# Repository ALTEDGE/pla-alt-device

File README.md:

# pla-alt-device

This repository contains the source code and hardware design files for the PLA ALT Avatar Motion Controller.

To compile the source code, use the [Arduino IDE](https://www.arduino.cc/en/software). After running the Arduino IDE, an `Arduino` folder is created in your Documents folder. Copy the `hardware` folder in this repo into that `Arudino` folder; then, the Arduino IDE should show "PLA ALT" as a board option.

The controller's hardware was designed using [EAGLE](https://www.autodesk.com/products/eagle/overview). Schematic and board files are located in the `eagle` folder.

## Brief user guide

The controller appears to the computer as a regular gaming joystick/controller. The [PLA ALT GUI](https://github.com/ALTEDGE/pla-alt-gui) must be running in order to use the controller to its full potential.

To reprogram the ALT controller, put it into programming mode by holding down the right joystick button while plugging into the computer; the LEDs should not turn on. After uploading new code through the IDE, reconnect the controller.

The ALT controller self-calibrates when it is first powered on. If recalibration is ever necessary, hold down the left joystick button while plugging into the computer. Release the button once the LEDs light up white. Calibration is finished once the LEDs return to blue.

### Licensing

The ALT controller's source code is licensed under the GNU GPLv3; see the LICENSE file in the top directory. The controller's hardware files (EAGLE schematic and board files) are licensed under the TAPR Open Hardware License; see the LICENSE file in the `eagle` folder.

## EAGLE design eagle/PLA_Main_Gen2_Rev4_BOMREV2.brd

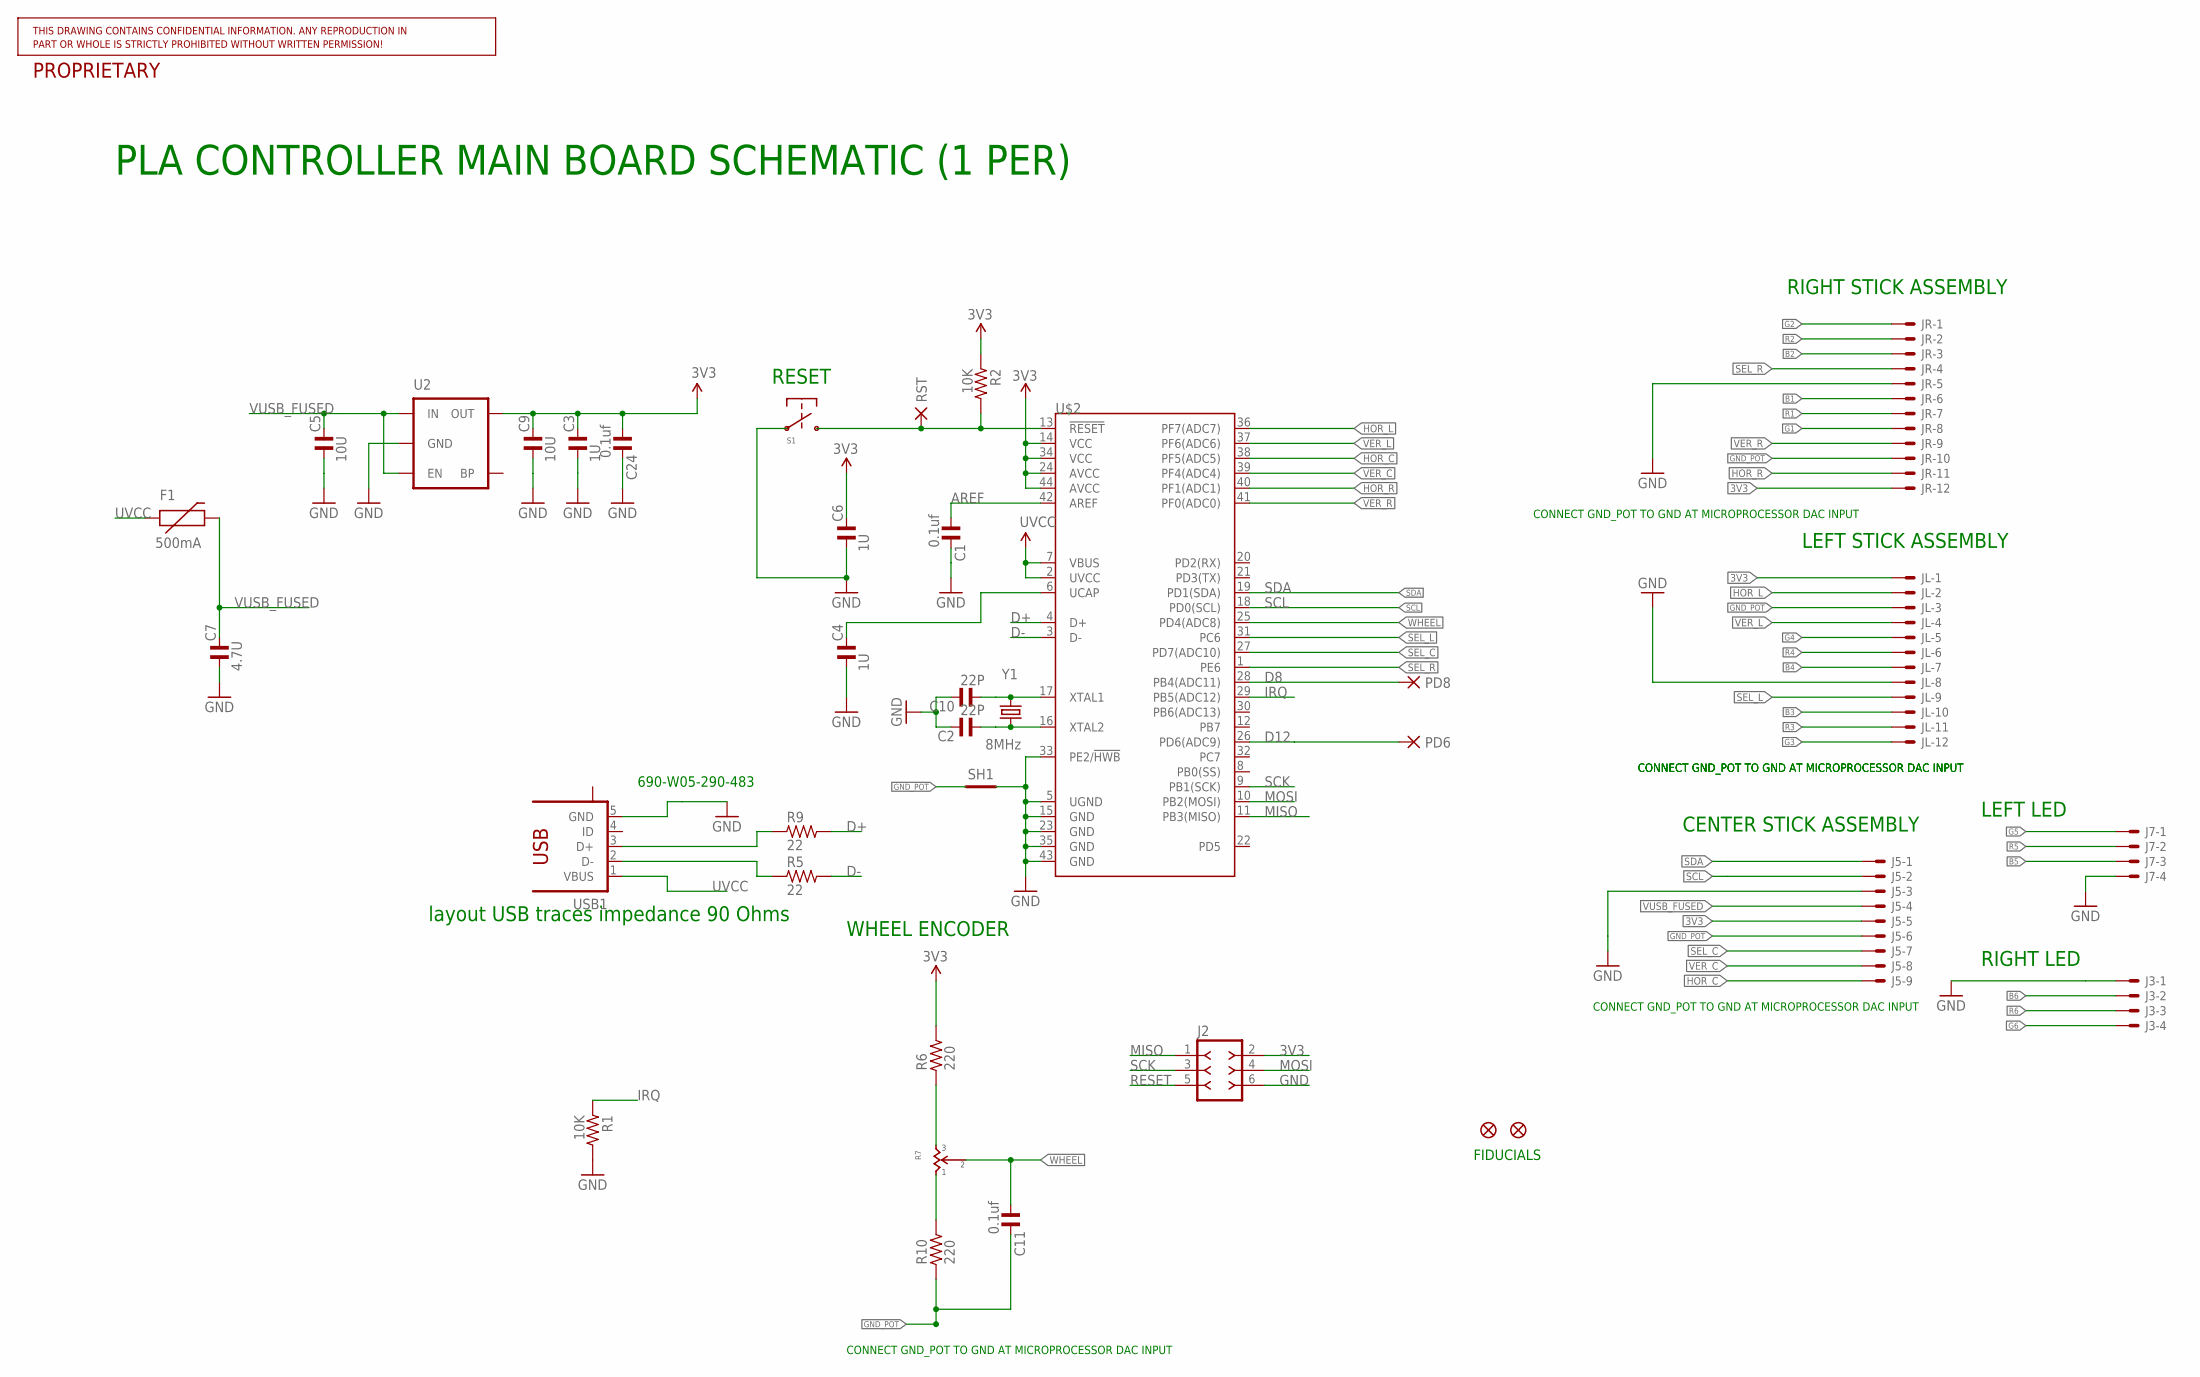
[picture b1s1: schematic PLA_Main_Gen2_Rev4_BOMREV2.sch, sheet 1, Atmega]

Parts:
C1, C11, C24: 0.1uf; C0603; PARTNO 64K2839
C2, C10: 22P; C0603; PARTNO 06035C220JAT2A
C3, C4, C6: 1U; C0603; PARTNO CL10B105KP8NNNC
C5, C9: 10U; C1206; PARTNO C3216X5R1H106K160AB
C7: 4.7U; C0603; PARTNO GRM188R61A475KE15D
F1: 500mA; PTC-1206; PARTNO NANOSMDH075F-02
J2: F-2X03-DIL-100; DIL-100-2X03; PARTNO *
J3, J7: SM04B-SRSS-TB; PARTNO SM04B-SRSS-TB(LF)(SN)
J5: SM09B-SRSS-TB; PARTNO SM09B-SRSS-TB
JL: SM12B-SRSS-TB; PARTNO SM12B-SRSS-TB(LF)(SN)
JP1, JP2: FIDUCIALUFIDUCIAL; MICRO-FIDUCIAL; PARTNO *
JR: SM12B-SRSS-TB; PARTNO SM12B-SRSS-TB(LF)(SN)
PD6, PD8: PAD-SMD12R; SMD12R
R1, R2: 10K; R0603; PARTNO ERJ-PA3J103V
R5, R9: 22; R0603; PARTNO ERJ-PA3J220V
R6, R10: 220; R0603; PARTNO ERJ-PA3J221V
R7: SV01A103AEA01R00; PARTNO SV01A103AEA01R00
RST: PAD-SMD10R; SMD10R
S1: KMR211GLFS; PARTNO KMR211GLFS
SH1: SHORTT5; SHORT_TOP-50; PARTNO *
U2: V_REG_LDOSMD; SOT23-5; PARTNO MIC5219-3.3YM5-TR
U$2: ATMEGA32U4QFN; QFN-44; PARTNO ATMEGA32U4-MU
USB1: 10118192-0001LF; PARTNO 10118192-0001LF
Y1: 8MHz; CRYSTAL-SMD-5X3; PARTNO ABM3B-8.000MHZ-B2-T

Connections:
3V3: C3.2, C6.2, C9.2, C24.1, J2.2, J5.5, JL.1, JR.12, R2.1, R6.2, U2.5 (OUT), U$2.14 (VCC), U$2.24 (AVCC), U$2.34 (VCC), U$2.44 (AVCC); also elsewhere on the board
AREF: C1.1, U$2.42 (AREF)
B1: JR.6; also elsewhere on the board
B2: JR.3; also elsewhere on the board
B3: JL.10; also elsewhere on the board
B4: JL.7; also elsewhere on the board
B5: J7.3; also elsewhere on the board
B6: J3.2; also elsewhere on the board
D8: PD8.PAD, U$2.28 (PB4(ADC11))
D12: PD6.PAD, U$2.26 (PD6(ADC9))
D+: R9.2, U$2.4 (D+)
D-: R5.2, U$2.3 (D-)
G1: JR.8; also elsewhere on the board
G2: JR.1; also elsewhere on the board
G3: JL.12; also elsewhere on the board
G4: JL.5; also elsewhere on the board
G5: J7.1; also elsewhere on the board
G6: J3.4; also elsewhere on the board
GND: C1.2, C2.2, C3.1, C4.1, C5.1, C6.1, C7.1, C9.1, C10.2, C24.2, J2.6, J3.1, J5.3, J7.4, JL.8, JR.5, R1.2, S1.1A (1), S1.1B (1), SH1.2, U2.2 (GND), U$2.5 (UGND), U$2.15 (GND), U$2.23 (GND), U$2.33 (PE2/!HWB), U$2.35 (GND), U$2.43 (GND), USB1.5 (GND); also elsewhere on the board
GND_POT: C11.2, J5.6, JL.3, JR.10, R10.1, SH1.1
HOR_C: J5.9, U$2.38 (PF5(ADC5))
HOR_L: JL.2, U$2.36 (PF7(ADC7))
HOR_R: JR.11, U$2.40 (PF1(ADC1))
IRQ: R1.1, U$2.29 (PB5(ADC12))
MISO: J2.1, U$2.11 (PB3(MISO))
MOSI: J2.4, U$2.10 (PB2(MOSI))
unnamed: C2.1, U$2.16 (XTAL2), Y1.1
unnamed: C10.1, U$2.17 (XTAL1), Y1.3 (2)
unnamed: C4.2, U$2.6 (UCAP)
unnamed: R6.1, R7.3
unnamed: R7.1, R10.2
R1: JR.7; also elsewhere on the board
R2: JR.2; also elsewhere on the board
R3: JL.11; also elsewhere on the board
R4: JL.6; also elsewhere on the board
R5: J7.2; also elsewhere on the board
R6: J3.3; also elsewhere on the board
RESET: J2.5, R2.2, RST.PAD, S1.2A (2), S1.2B (2), U$2.13 (!RESET)
SCK: J2.3, U$2.9 (PB1(SCK))
SCL: J5.2, U$2.18 (PD0(SCL)); also elsewhere on the board
SDA: J5.1, U$2.19 (PD1(SDA)); also elsewhere on the board
SEL_C: J5.7, U$2.27 (PD7(ADC10))
SEL_L: JL.9, U$2.31 (PC6)
SEL_R: JR.4, U$2.1 (PE6)
USB_N: R5.1, USB1.2 (D-)
USB_P: R9.1, USB1.3 (D+)
UVCC: F1.1, U$2.2 (UVCC), U$2.7 (VBUS), USB1.1 (VBUS)
VER_C: J5.8, U$2.39 (PF4(ADC4))
VER_L: JL.4, U$2.37 (PF6(ADC6))
VER_R: JR.9, U$2.41 (PF0(ADC0))
VUSB_FUSED: C5.2, C7.2, F1.2, J5.4, U2.1 (IN), U2.3 (EN); also elsewhere on the board
WHEEL: C11.1, R7.2, R7.2A (2), U$2.25 (PD4(ADC8))

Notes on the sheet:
690-W05-290-483
layout USB traces impedance 90 Ohms
LEFT STICK ASSEMBLY
CONNECT GND_POT TO GND AT MICROPROCESSOR DAC INPUT
RIGHT STICK ASSEMBLY
CENTER STICK ASSEMBLY
WHEEL ENCODER
RESET
LEFT LED
RIGHT LED
FIDUCIALS
PLA CONTROLLER MAIN BOARD SCHEMATIC (1 PER)

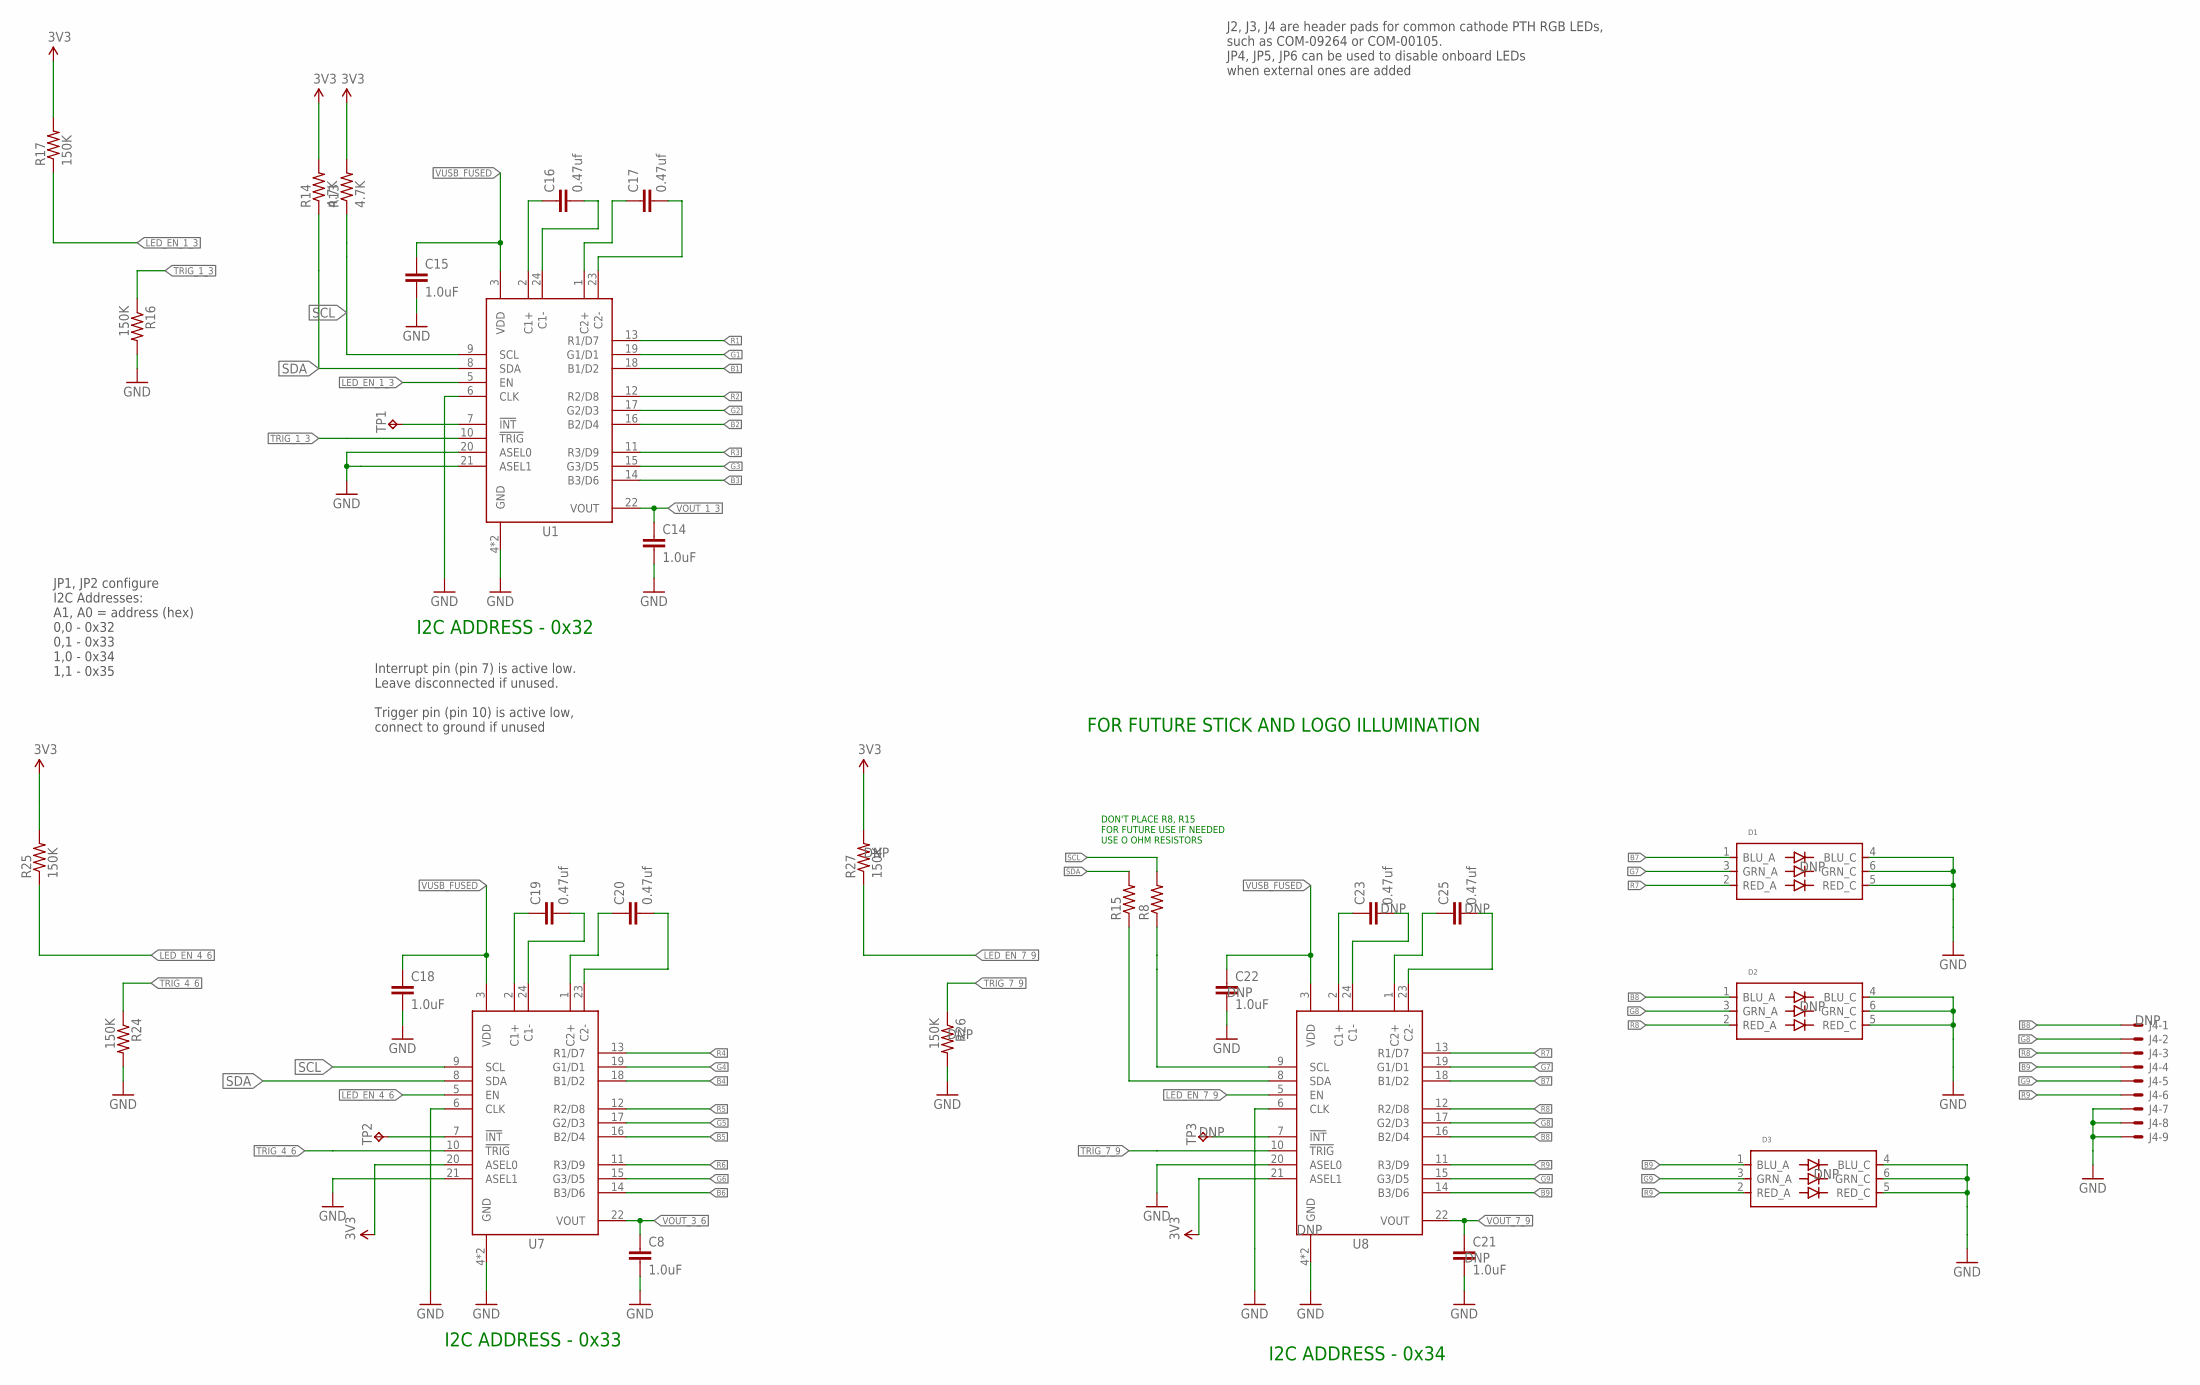
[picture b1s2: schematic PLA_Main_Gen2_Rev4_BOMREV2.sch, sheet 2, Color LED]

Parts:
C8, C14, C15, C18, C21, C22: 1.0uF; 0603-CAP; PARTNO CL10B105KP8NNNC
C16, C17, C19, C20, C23, C25: 0.47uf; 0603-CAP; PARTNO 0603YG474ZAT2A
D1, D2, D3: XZFBBM2ACRDG92W-3; PARTNO XZFBBM2ACRDG92W-3
J4: BM09B-SRSS-TB; PARTNO BM09B-SRSS-TB
R8, R15: 4.7KOHM-1/10W-1%(0603); 0603-RES; PARTNO ERJ-PA3J472V
R13, R14: 4.7K; 0603-RES; PARTNO ERJ-PA3J472V
R16, R17, R24, R25, R26, R27: 150K; 0603-RES; PARTNO ERJ-PA3J154V
TP1, TP2, TP3: TP-040; PARTNO *
U1, U7, U8: LP55231WQFN; WQFN-24; PARTNO LP55231SQX/NOPB

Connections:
3V3: R13.2, R14.2, R17.2, R25.2, R27.2, U7.20 (ASEL0), U8.21 (ASEL1); also elsewhere on the board
B1: U1.18 (B1/D2); also elsewhere on the board
B2: U1.16 (B2/D4); also elsewhere on the board
B3: U1.14 (B3/D6); also elsewhere on the board
B4: U7.18 (B1/D2); also elsewhere on the board
B5: U7.16 (B2/D4); also elsewhere on the board
B6: U7.14 (B3/D6); also elsewhere on the board
B7: D1.1 (BLU_A), U8.18 (B1/D2)
B8: D2.1 (BLU_A), J4.1, U8.16 (B2/D4)
B9: D3.1 (BLU_A), J4.4, U8.14 (B3/D6)
G1: U1.19 (G1/D1); also elsewhere on the board
G2: U1.17 (G2/D3); also elsewhere on the board
G3: U1.15 (G3/D5); also elsewhere on the board
G4: U7.19 (G1/D1); also elsewhere on the board
G5: U7.17 (G2/D3); also elsewhere on the board
G6: U7.15 (G3/D5); also elsewhere on the board
G7: D1.3 (GRN_A), U8.19 (G1/D1)
G8: D2.3 (GRN_A), J4.2, U8.17 (G2/D3)
G9: D3.3 (GRN_A), J4.5, U8.15 (G3/D5)
GND: C8.2, C14.2, C15.2, C18.2, C21.2, C22.2, D1.4 (BLU_C), D1.5 (RED_C), D1.6 (GRN_C), D2.4 (BLU_C), D2.5 (RED_C), D2.6 (GRN_C), D3.4 (BLU_C), D3.5 (RED_C), D3.6 (GRN_C), J4.7, J4.8, J4.9, R16.2, R24.2, R26.2, U1.4 (GND), U1.6 (CLK), U1.20 (ASEL0), U1.21 (ASEL1), U1.EP (GND), U7.4 (GND), U7.6 (CLK), U7.21 (ASEL1), U7.EP (GND), U8.4 (GND), U8.6 (CLK), U8.20 (ASEL0), U8.EP (GND); also elsewhere on the board
LED_EN_1_3: R17.1, U1.5 (EN)
LED_EN_4_6: R25.1, U7.5 (EN)
LED_EN_7_9: R27.1, U8.5 (EN)
unnamed: TP1.1, U1.7 (!INT)
unnamed: C19.1, U7.2 (C1+)
unnamed: C19.2, U7.24 (C1-)
unnamed: C16.1, U1.2 (C1+)
unnamed: C16.2, U1.24 (C1-)
unnamed: C17.1, U1.1 (C2+)
unnamed: C17.2, U1.23 (C2-)
unnamed: C20.1, U7.1 (C2+)
unnamed: C20.2, U7.23 (C2-)
unnamed: TP2.1, U7.7 (!INT)
unnamed: C23.1, U8.2 (C1+)
unnamed: C23.2, U8.24 (C1-)
unnamed: C25.1, U8.1 (C2+)
unnamed: C25.2, U8.23 (C2-)
unnamed: TP3.1, U8.7 (!INT)
R1: U1.13 (R1/D7); also elsewhere on the board
R2: U1.12 (R2/D8); also elsewhere on the board
R3: U1.11 (R3/D9); also elsewhere on the board
R4: U7.13 (R1/D7); also elsewhere on the board
R5: U7.12 (R2/D8); also elsewhere on the board
R6: U7.11 (R3/D9); also elsewhere on the board
R7: D1.2 (RED_A), U8.13 (R1/D7)
R8: D2.2 (RED_A), J4.3, U8.12 (R2/D8)
R9: D3.2 (RED_A), J4.6, U8.11 (R3/D9)
SCL: R8.2, R13.1, U1.9 (SCL), U7.9 (SCL); also elsewhere on the board
SCL2: R8.1, U8.9 (SCL)
SDA: R14.1, R15.2, U1.8 (SDA), U7.8 (SDA); also elsewhere on the board
SDA2: R15.1, U8.8 (SDA)
TRIG_1_3: R16.1, U1.10 (!TRIG)
TRIG_4_6: R24.1, U7.10 (!TRIG)
TRIG_7_9: R26.1, U8.10 (!TRIG)
VOUT_1_3: C14.1, U1.22 (VOUT)
VOUT_3_6: C8.1, U7.22 (VOUT)
VOUT_7_9: C21.1, U8.22 (VOUT)
VUSB_FUSED: C15.1, C18.1, C22.1, U1.3 (VDD), U7.3 (VDD), U8.3 (VDD); also elsewhere on the board

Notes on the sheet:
JP1, JP2 configure I2C Addresses: A1, A0 = address (hex) 0,0 - 0x32 0,1 - 0x33 1,0 - 0x34 1,1 - 0x35
J2, J3, J4 are header pads for common cathode PTH RGB LEDs, such as COM-09264 or COM-00105. JP4, JP5, JP6 can be used to disable onboard LEDs when external ones are added
Interrupt pin (pin 7) is active low. Leave disconnected if unused. Trigger pin (pin 10) is active low, connect to ground if unused
FOR FUTURE STICK AND LOGO ILLUMINATION
I2C ADDRESS - 0x32
I2C ADDRESS - 0x33
I2C ADDRESS - 0x34
DON'T PLACE R8, R15 FOR FUTURE USE IF NEEDED USE O OHM RESISTORS

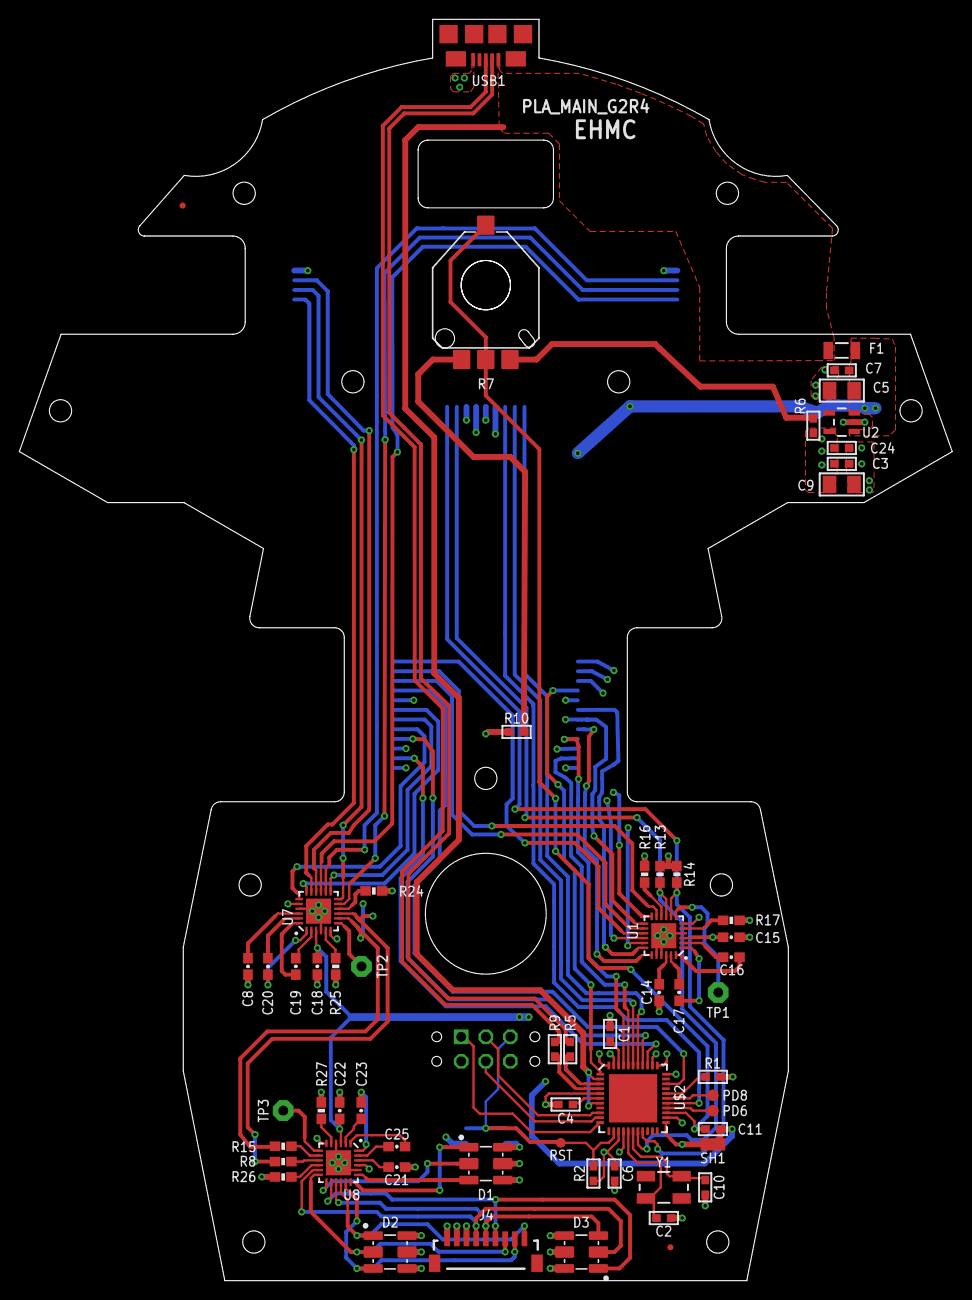
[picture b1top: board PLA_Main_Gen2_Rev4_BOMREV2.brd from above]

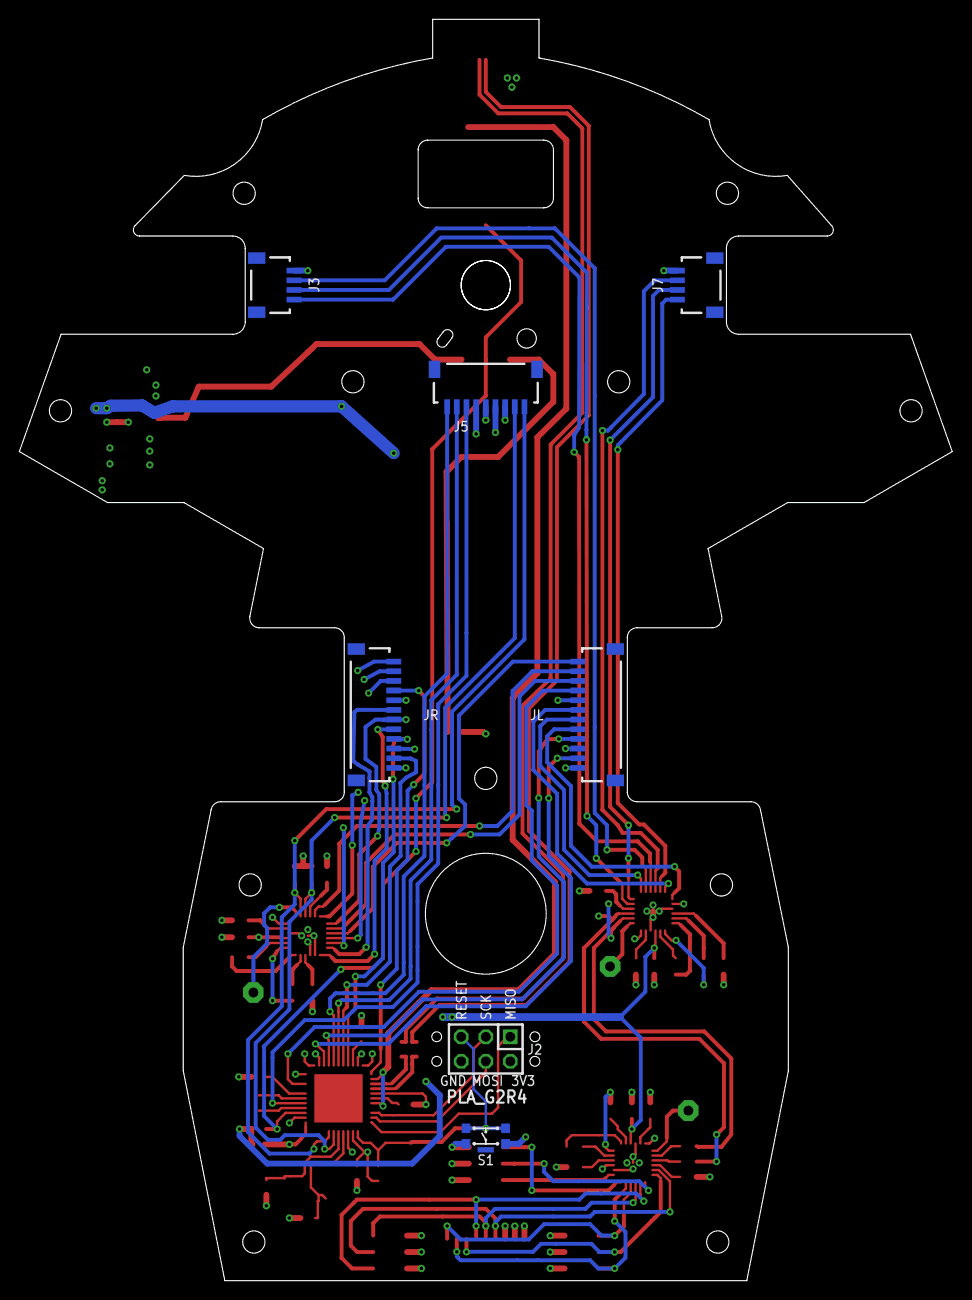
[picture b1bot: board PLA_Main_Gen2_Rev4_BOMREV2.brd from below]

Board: 4 copper layers, 96.5 x 130.5 mm, 70 parts (7 on the bottom side), 87 nets.

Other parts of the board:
U$3: FAB_FRAME_ANSI-A
U$4: FAB_DOCFIELD_GENERIC

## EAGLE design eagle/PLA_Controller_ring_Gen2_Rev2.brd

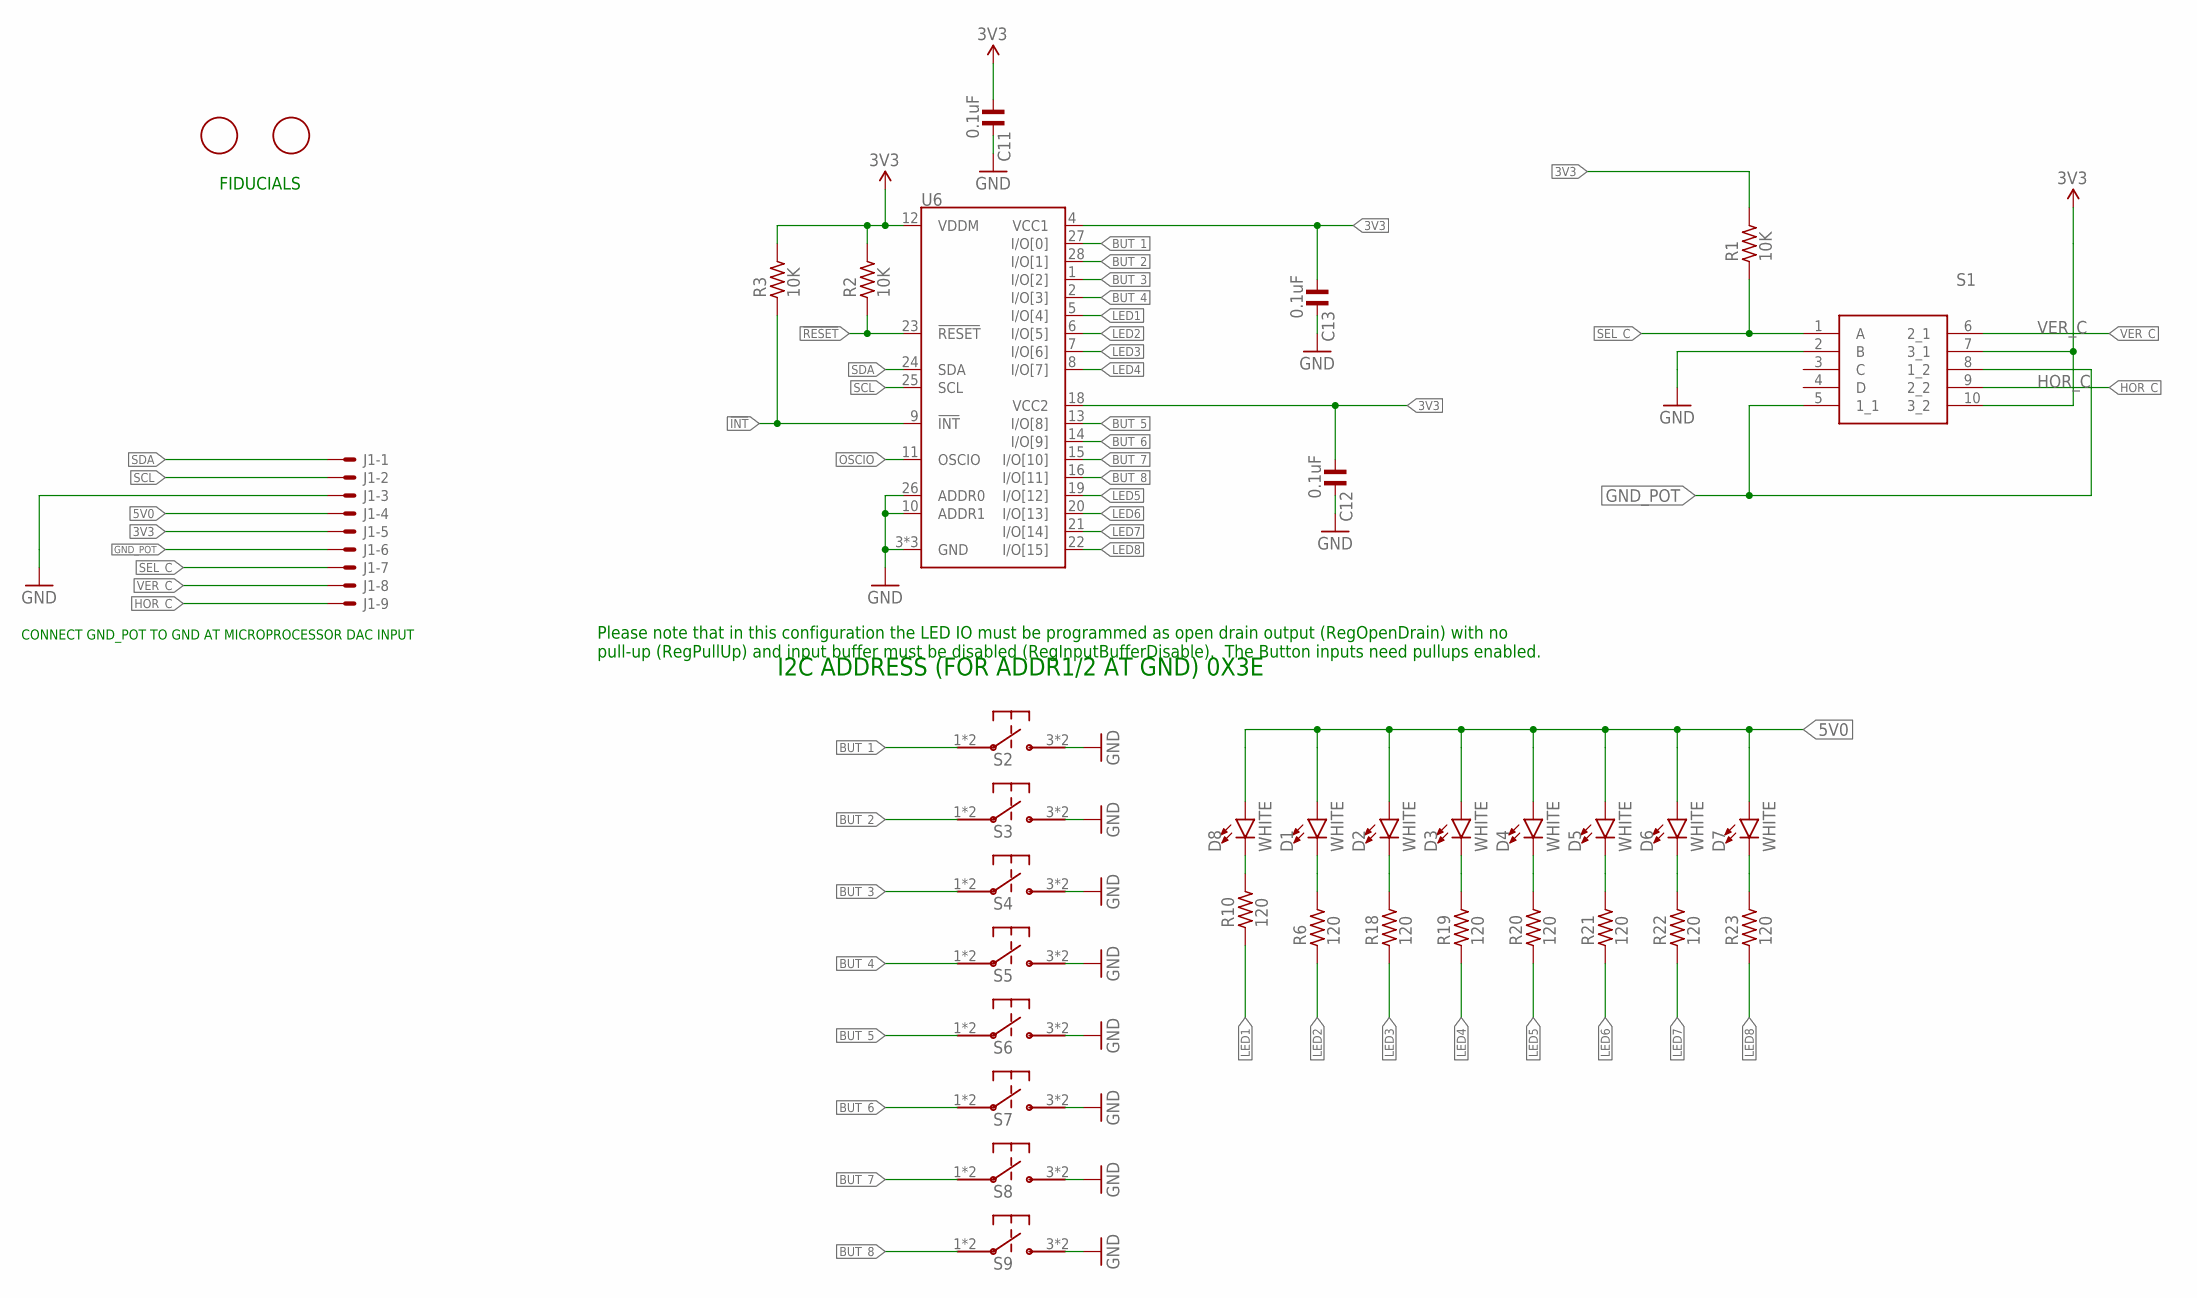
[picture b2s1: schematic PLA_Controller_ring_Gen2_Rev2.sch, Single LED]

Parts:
C11, C12, C13: 0.1uF; C0603; PARTNO CAP-00810
D1, D2, D3, D4, D5, D6, D7, D8: WHITE; LED-0603; PARTNO QBLP601-IW
J1: BM09B-SRSS-TB; PARTNO BM09B-SRSS-TB
R1, R2, R3: 10K; R0603; PARTNO ERJ-2GEJ103X
R6, R10, R18, R19, R20, R21, R22, R23: 120; R0603; PARTNO ERJ-PA3J121V
S1: RKJXV1224005; PARTNO RKJXV1224005
S2, S3, S4, S5, S6, S7, S8, S9: TL3315NF100Q; PARTNO TL3315NF100Q
U6: SX1509; QFN-28; PARTNO SX1509BIULTRT
U$8, U$9: FIDUCIAL; FIDUCIAL_1MM; PARTNO *

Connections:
3V3: C11.1, C12.1, C13.1, J1.5, R1.2, R2.2, R3.2, S1.7 (3_1), S1.10 (3_2), U6.4 (VCC1), U6.12 (VDDM), U6.18 (VCC2)
5V0: D1.A, D2.A, D3.A, D4.A, D5.A, D6.A, D7.A, D8.A, J1.4
!INT: R3.1, U6.9 (!INT)
!RESET: R2.1, U6.23 (!RESET)
BUT_1: S2.1, S2.2, U6.27 (I/O[0])
BUT_2: S3.1, S3.2, U6.28 (I/O[1])
BUT_3: S4.1, S4.2, U6.1 (I/O[2])
BUT_4: S5.1, S5.2, U6.2 (I/O[3])
BUT_5: S6.1, S6.2, U6.13 (I/O[8])
BUT_6: S7.1, S7.2, U6.14 (I/O[9])
BUT_7: S8.1, S8.2, U6.15 (I/O[10])
BUT_8: S9.1, S9.2, U6.16 (I/O[11])
GND: C11.2, C12.2, C13.2, J1.3, S1.2 (B), S2.3, S2.4, S3.3, S3.4, S4.3, S4.4, S5.3, S5.4, S6.3, S6.4, S7.3, S7.4, S8.3, S8.4, S9.3, S9.4, U6.3 (GND), U6.10 (ADDR1), U6.17 (GND), U6.26 (ADDR0), U6.29 (GND)
GND_POT: J1.6, S1.5 (1_1), S1.8 (1_2)
HOR_C: J1.9, S1.9 (2_2)
LED1: R10.1, U6.5 (I/O[4])
LED2: R6.1, U6.6 (I/O[5])
LED3: R18.1, U6.7 (I/O[6])
LED4: R19.1, U6.8 (I/O[7])
LED5: R20.1, U6.19 (I/O[12])
LED6: R21.1, U6.20 (I/O[13])
LED7: R22.1, U6.21 (I/O[14])
LED8: R23.1, U6.22 (I/O[15])
unnamed: D1.C, R6.2
unnamed: D8.C, R10.2
unnamed: D2.C, R18.2
unnamed: D3.C, R19.2
unnamed: D4.C, R20.2
unnamed: D5.C, R21.2
unnamed: D6.C, R22.2
unnamed: D7.C, R23.2
OSCIO: U6.11 (OSCIO)
SCL: J1.2, U6.25 (SCL)
SDA: J1.1, U6.24 (SDA)
SEL_C: J1.7, R1.1, S1.1 (A)
VER_C: J1.8, S1.6 (2_1)

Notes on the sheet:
Please note that in this configuration the LED IO must be programmed as open drain output (RegOpenDrain) with no pull-up (RegPullUp) and input buffer must be disabled (RegInputBufferDisable). The Button inputs need pullups enabled.
CONNECT GND_POT TO GND AT MICROPROCESSOR DAC INPUT
I2C ADDRESS (FOR ADDR1/2 AT GND) 0X3E
FIDUCIALS

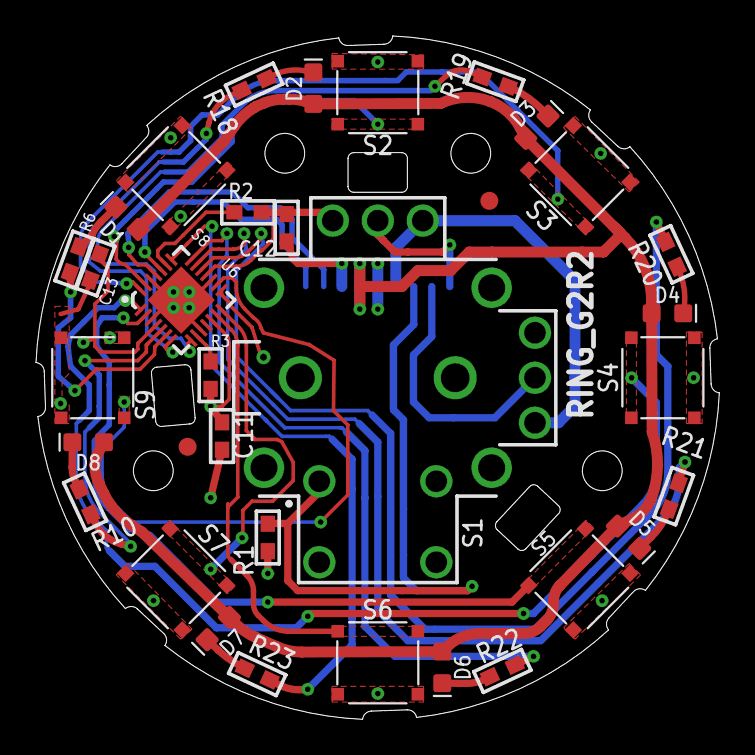
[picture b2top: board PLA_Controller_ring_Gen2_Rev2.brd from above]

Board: 4 copper layers, 38.0 x 38.0 mm, 41 parts (1 on the bottom side), 35 nets.

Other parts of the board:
U$2, U$5, U$6, U$7: 086
U$3: FAB_FRAME_ANSI-A
U$4: FAB_DOCFIELD_GENERIC

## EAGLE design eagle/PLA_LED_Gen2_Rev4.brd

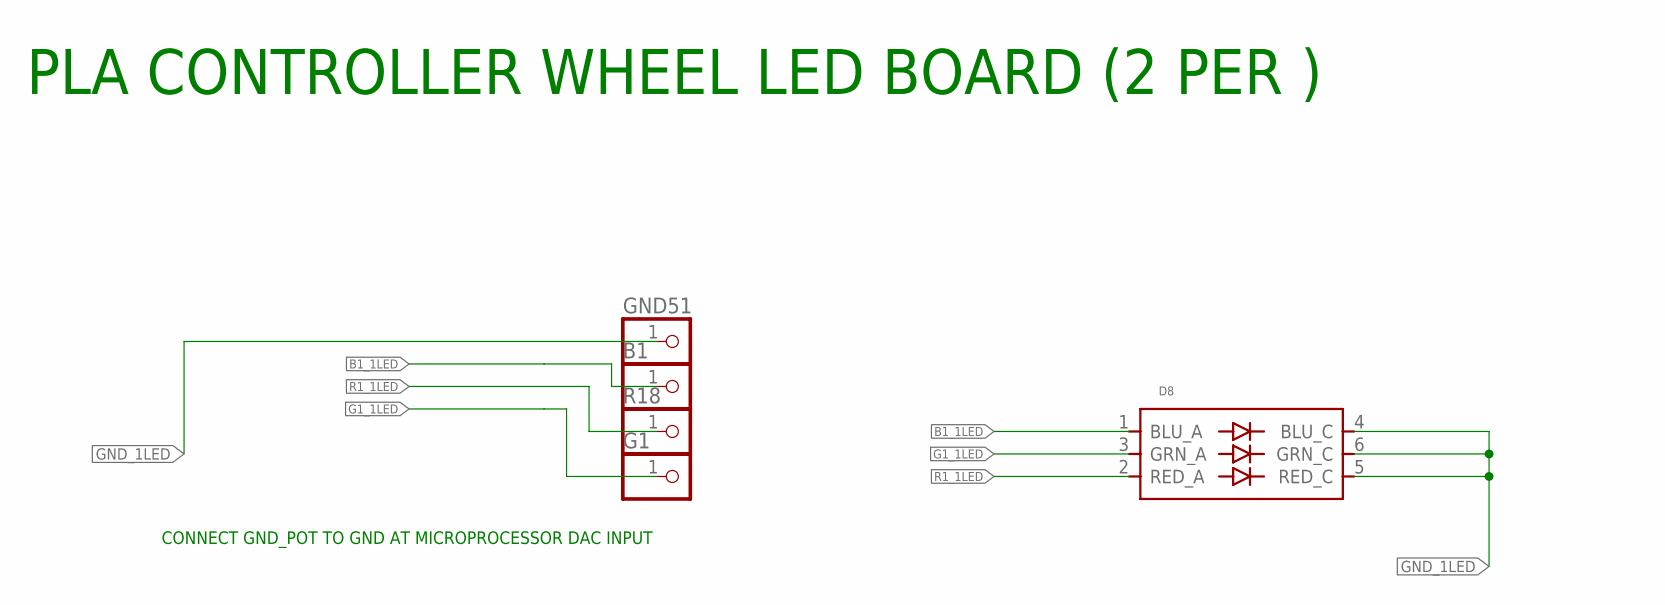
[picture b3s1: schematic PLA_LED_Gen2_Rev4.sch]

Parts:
B1: PINHD-1X1; 1X01; PARTNO *
D8: XZFBBM2ACRDG92W-3; PARTNO XZFBBM2ACRDG92W-3
G1: PINHD-1X1; 1X01; PARTNO *
GND51: PINHD-1X1; 1X01; PARTNO *
R18: PINHD-1X1; 1X01; PARTNO *

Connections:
B1_1LED: B1.1, D8.1 (BLU_A)
G1_1LED: D8.3 (GRN_A), G1.1
GND_1LED: D8.4 (BLU_C), D8.5 (RED_C), D8.6 (GRN_C), GND51.1
R1_1LED: D8.2 (RED_A), R18.1

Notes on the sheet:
CONNECT GND_POT TO GND AT MICROPROCESSOR DAC INPUT
PLA CONTROLLER WHEEL LED BOARD (2 PER )

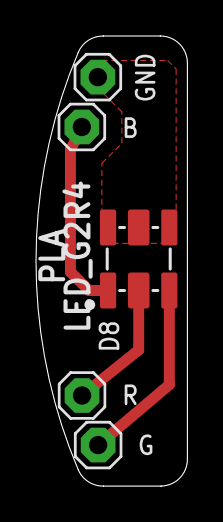
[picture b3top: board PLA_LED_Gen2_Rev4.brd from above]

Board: 4 copper layers, 8.4 x 25.0 mm, 7 parts (0 on the bottom side), 4 nets.

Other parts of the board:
U$3: FAB_FRAME_ANSI-A
U$4: FAB_DOCFIELD_GENERIC

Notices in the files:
parts and their libraries:
rc-master-smd: Copyright (C) 2007-2008, Bob Starr
dfabdoc: Copyright (C) 2008, Bob Starr
SparkFun-DigitalIC: Licensing: CC v3.0 Share-Alike You are welcome to use this library for commercial purposes.
